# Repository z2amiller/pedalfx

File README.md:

# pedalfx

This is my repository for publicly-available guitar pedal/effects stuff.
(Documentation, gerber files, schematics, etc)

KiCad project templates live in `template/` (symlink
`~/Documents/KiCad/10.0/template` to it). The shared DRC rules, text defaults
and the `pedal-fleet` CLI that keeps templates and boards in sync are in
`template/_fleet/`.

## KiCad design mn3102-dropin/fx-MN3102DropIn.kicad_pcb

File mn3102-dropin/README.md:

# mn3102-dropin — CD4047B replacement for the MN3102 BBD clock driver

Replaces the Panasonic MN3102 (clock generator for MN3204/05/07/08/09 BBDs) with
a CD4047B plus four passives. Two ways to use it:

## 1. As a schematic block in a new design

Add `clock_3102_cd4047.kicad_sch` as a hierarchical sheet wherever a host
schematic shows an MN3102. The 8 sheet pins mirror the MN3102's DIP-8 pins
one-for-one:

| Sheet pin | MN3102 pin | Role                                           |
| --------- | ---------- | ---------------------------------------------- |
| VDD       | 1          | 4–10V supply (feed from the filtered BBD rail) |
| CP1       | 2          | Clock out (4047 Q)                             |
| GND       | 3          | Ground                                         |
| CP2       | 4          | Clock out, antiphase (4047 Q̄)                  |
| OX3       | 5          | C-drive (4047 pin 1) — timing cap OX3→OX1      |
| OX2       | 6          | R-drive (4047 pin 2) — timing resistor OX2→OX1 |
| OX1       | 7          | RC common / oscillator input (4047 pin 3)      |
| VGG_OUT   | 8          | 15/16·VDD (≈14/15) for the BBD's VGG pin       |

Wire the host's existing timing R, C, and LFO network to OX1/OX2/OX3 exactly as
they were wired to the MN3102. Both self-oscillation (R + C) and current-driven
hosts (Julia/Caesar/PizzaPizza style: OX2 open, LFO current into OX1) work
unchanged. f_CP = 1/(4.4·R·C) at 50% duty.

## 2. As a DIP-8 adapter board

The root sheet (`fx-MN3102DropIn.kicad_sch`) adds J1, a DIP-8 machined-pin
header footprint, so the same block can be laid out as a tiny board that plugs
into an existing MN3102 socket.

### Package fit inside the DIP-8 outline

The DIP-8 pad ring's inner edge is 3.01mm from the board centerline (pads Ø1.6
on 7.62mm rows). Measured pad-field extents (KiCad footprints):

| Package                                  | Pad field half-extent        | Fits between rows?                   |
| ---------------------------------------- | ---------------------------- | ------------------------------------ |
| SOIC-14 (leads across)                   | 3.45mm                       | **No — overlaps DIP pads by 0.44mm** |
| TSSOP-14 rotated 90° (leads along board) | 2.15mm across / 3.60mm along | **Yes, ≥0.5mm clear**                |

**Recommended construction: everything on top, bare bottom.** Board ~12.7mm
long: TSSOP-14 rotated 90° in the middle between the pin rows, two 0603s on each
end tongue (~2.5mm overhang past the socket ends). Bare bottom = the board seats
flush on the socket, no standoff/height concerns at all.

Overhang clearance, verified against fx-PizzaPizza: nearest on-axis parts are
R9/R11 (0603, ~0.8mm tall) 3.4mm past one socket end — the overhang flies ~3.5mm
above them at socket-top height; the other end is clear for 8mm+. In general
only tall neighbors matter (electrolytics, box film caps, adjacent socketed ICs)
— check per host, especially through-hole builds.

Alternate (zero overhang): passives on the underside between the pin rows — then
use collared machined-pin strips (≥1.5mm standoff) so back-side parts (≤0.9mm
with solder) clear the socket face.

VGG cap note: C2 is optional insurance, not functional — the BBD's VGG pin draws
no DC current and many hosts already have a cap on that net (PizzaPizza: C21
22µF). 100nF is plenty (filter corner ~1.7kHz vs 50-200kHz clock); DNP it if
space is tight. Lowest-profile alternates, all Basic tier 0402: 1k C11702, 15k
C25756, 100nF 50V C307331 (~0.55mm tall).

## BOM (JLC, snapshot 2026-08)

| Ref | Value                | Package  | LCSC     | Tier     |
| --- | -------------------- | -------- | -------- | -------- |
| U1  | CD4047BPWR (adapter) | TSSOP-14 | C2652491 | Extended |
| R1  | 1k                   | 0603     | C21190   | Basic    |
| R2  | 15k                  | 0603     | C22809   | Basic    |
| C1  | 100n                 | 0603     | C14663   | Basic    |
| C2  | 100n (optional)      | 0603     | C14663   | Basic    |

**U1 sourcing reality** (live-checked 2026-08-08): the TSSOP-14 CD4047BPWR is
out of stock at JLC/LCSC (global-sourcing/notify-me only), but Mouser/DigiKey
stock it (~$0.30-0.60). Adapter plan: have JLC assemble the four Basic passives,
hand-stencil the TSSOP at home. For **in-design use** (full pedal board, no size
constraint), swap U1's footprint to SOIC-14 and use **CD4047BM96, LCSC C46538**
(35k+ stock) for normal JLC assembly.

Do **not** substitute 74HC4047 (6V max). CD4047B/HEF4047B only. Timing cap in
the host must be C0G/NP0.

Full design rationale, datasheet references, and caveats (clock cross-point,
drive limits for 4096-stage BBDs): `~/Claude/cd4047-mn3102-clock-reference.md`.
Verification: ERC 0/0, netlist checked against golden connectivity map
(kicad-cli 10.0.4).

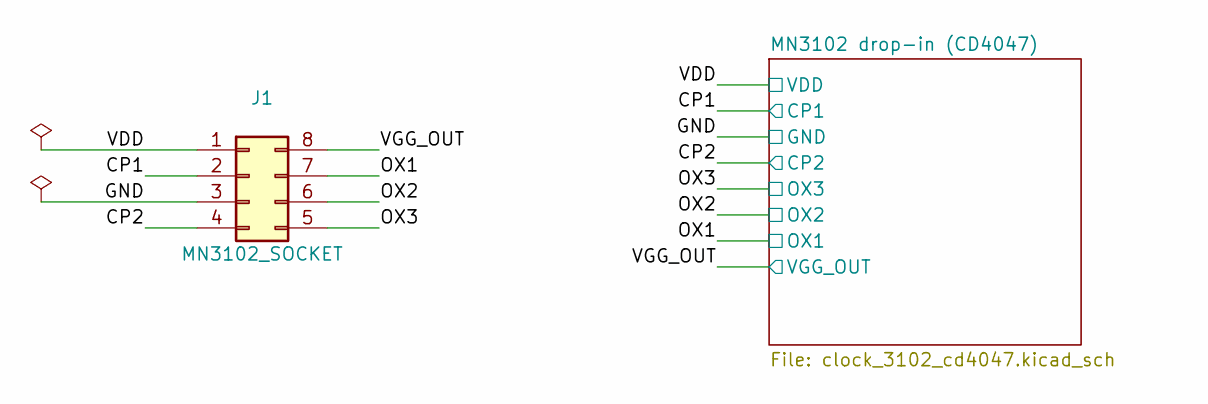
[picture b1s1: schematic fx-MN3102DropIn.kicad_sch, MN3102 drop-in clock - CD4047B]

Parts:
J1: MN3102_SOCKET; DIP-8_W7.62mm

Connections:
/CP1: J1.2; also elsewhere on the board
/CP2: J1.4; also elsewhere on the board
/GND: J1.3; also elsewhere on the board
/OX1: J1.7; also elsewhere on the board
/OX2: J1.6; also elsewhere on the board
/OX3: J1.5; also elsewhere on the board
/VDD: J1.1; also elsewhere on the board
/VGG_OUT: J1.8; also elsewhere on the board

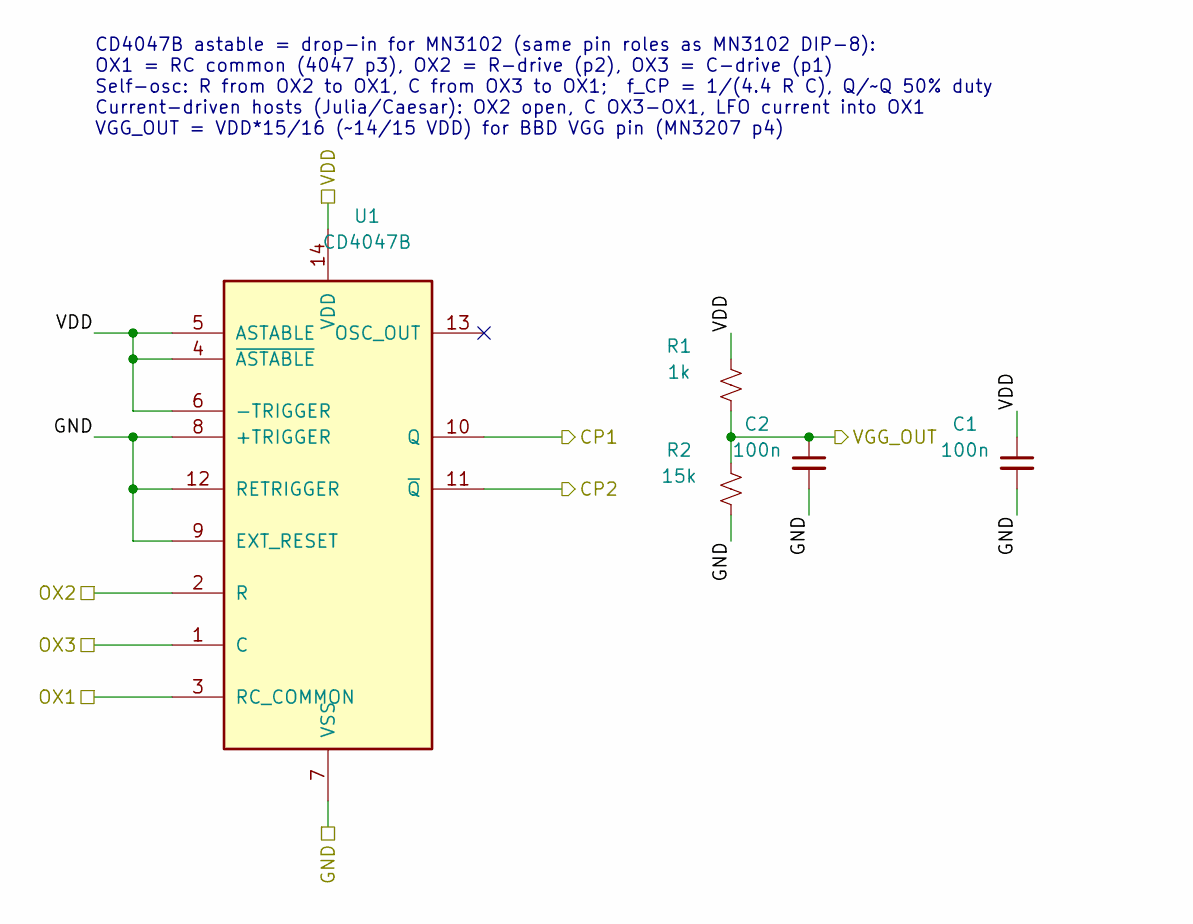
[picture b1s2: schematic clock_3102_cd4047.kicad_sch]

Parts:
C1, C2: 100n; C_0603_1608Metric; LCSC C14663
R1: 1k; R_0603_1608Metric; LCSC C21190
R2: 15k; R_0603_1608Metric; LCSC C22809
U1: CD4047B; TSSOP-14_4.4x5mm_P0.65mm; LCSC C2652491

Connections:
/CP1: U1.10 (Q); also elsewhere on the board
/CP2: U1.11 (~Q); also elsewhere on the board
/GND: C1.2, C2.2, R2.2, U1.7 (VSS), U1.8 (+TRIGGER), U1.9 (EXT_RESET), U1.12 (RETRIGGER); also elsewhere on the board
/OX1: U1.3 (RC_COMMON); also elsewhere on the board
/OX2: U1.2 (R); also elsewhere on the board
/OX3: U1.1 (C); also elsewhere on the board
/VDD: C1.1, R1.1, U1.4 (~ASTABLE), U1.5 (ASTABLE), U1.6 (-TRIGGER), U1.14 (VDD); also elsewhere on the board
/VGG_OUT: C2.1, R1.2, R2.1; also elsewhere on the board

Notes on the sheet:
CD4047B astable = drop-in for MN3102 (same pin roles as MN3102 DIP-8): OX1 = RC common (4047 p3), OX2 = R-drive (p2), OX3 = C-drive (p1) Self-osc: R from OX2 to OX1, C from OX3 to OX1; f_CP = 1/(4.4 R C), Q/~Q 50% duty Current-driven hosts (Julia/Caesar): OX2 open, C OX3-OX1, LFO current into OX1 V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

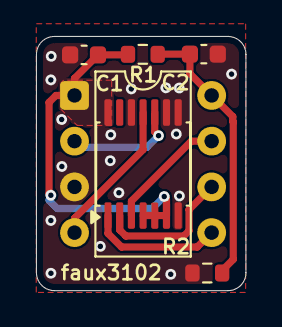
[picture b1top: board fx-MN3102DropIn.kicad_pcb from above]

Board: 2 copper layers, 11.6 x 14.1 mm, 6 parts (0 on the bottom side), 8 nets.

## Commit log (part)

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2025-08-12 Add a doc about JLCPCB assembly for guitar effects.
2025-08-13 Update JLCPCBA.md - add parts library info
2025-08-13 Add a doc for the octavio pedal.
2025-08-17 Move JLC PCBA guide to docs
2025-08-17 Add a config.yaml file
2025-09-08 Build files for the Octavio
2026-01-09 Add pitfalls and tips for designing effects PCBs
    This document outlines common pitfalls and tips for designing effects PCBs, including mistakes to avoid and helpful design practices.
2026-01-09 Fix image syntax in pitfalls-and-tips.md
2026-01-11 Add kicad-specific gitignore
2026-01-11 Add a template for a full-sized 125B board.
2026-01-11 New template for a 'normal sized' 125B SMD layout
2026-01-11 Fix gitignroe for jlcpcb dir
2026-02-21 Update Full 125B template
2026-04-20 Update Full-board 125B template.
2026-04-20 Update: Some tweaks to the normal 125B template.
2026-04-20 Add a template for a 125B faceplate.
2026-04-20 Fix template PCB.
